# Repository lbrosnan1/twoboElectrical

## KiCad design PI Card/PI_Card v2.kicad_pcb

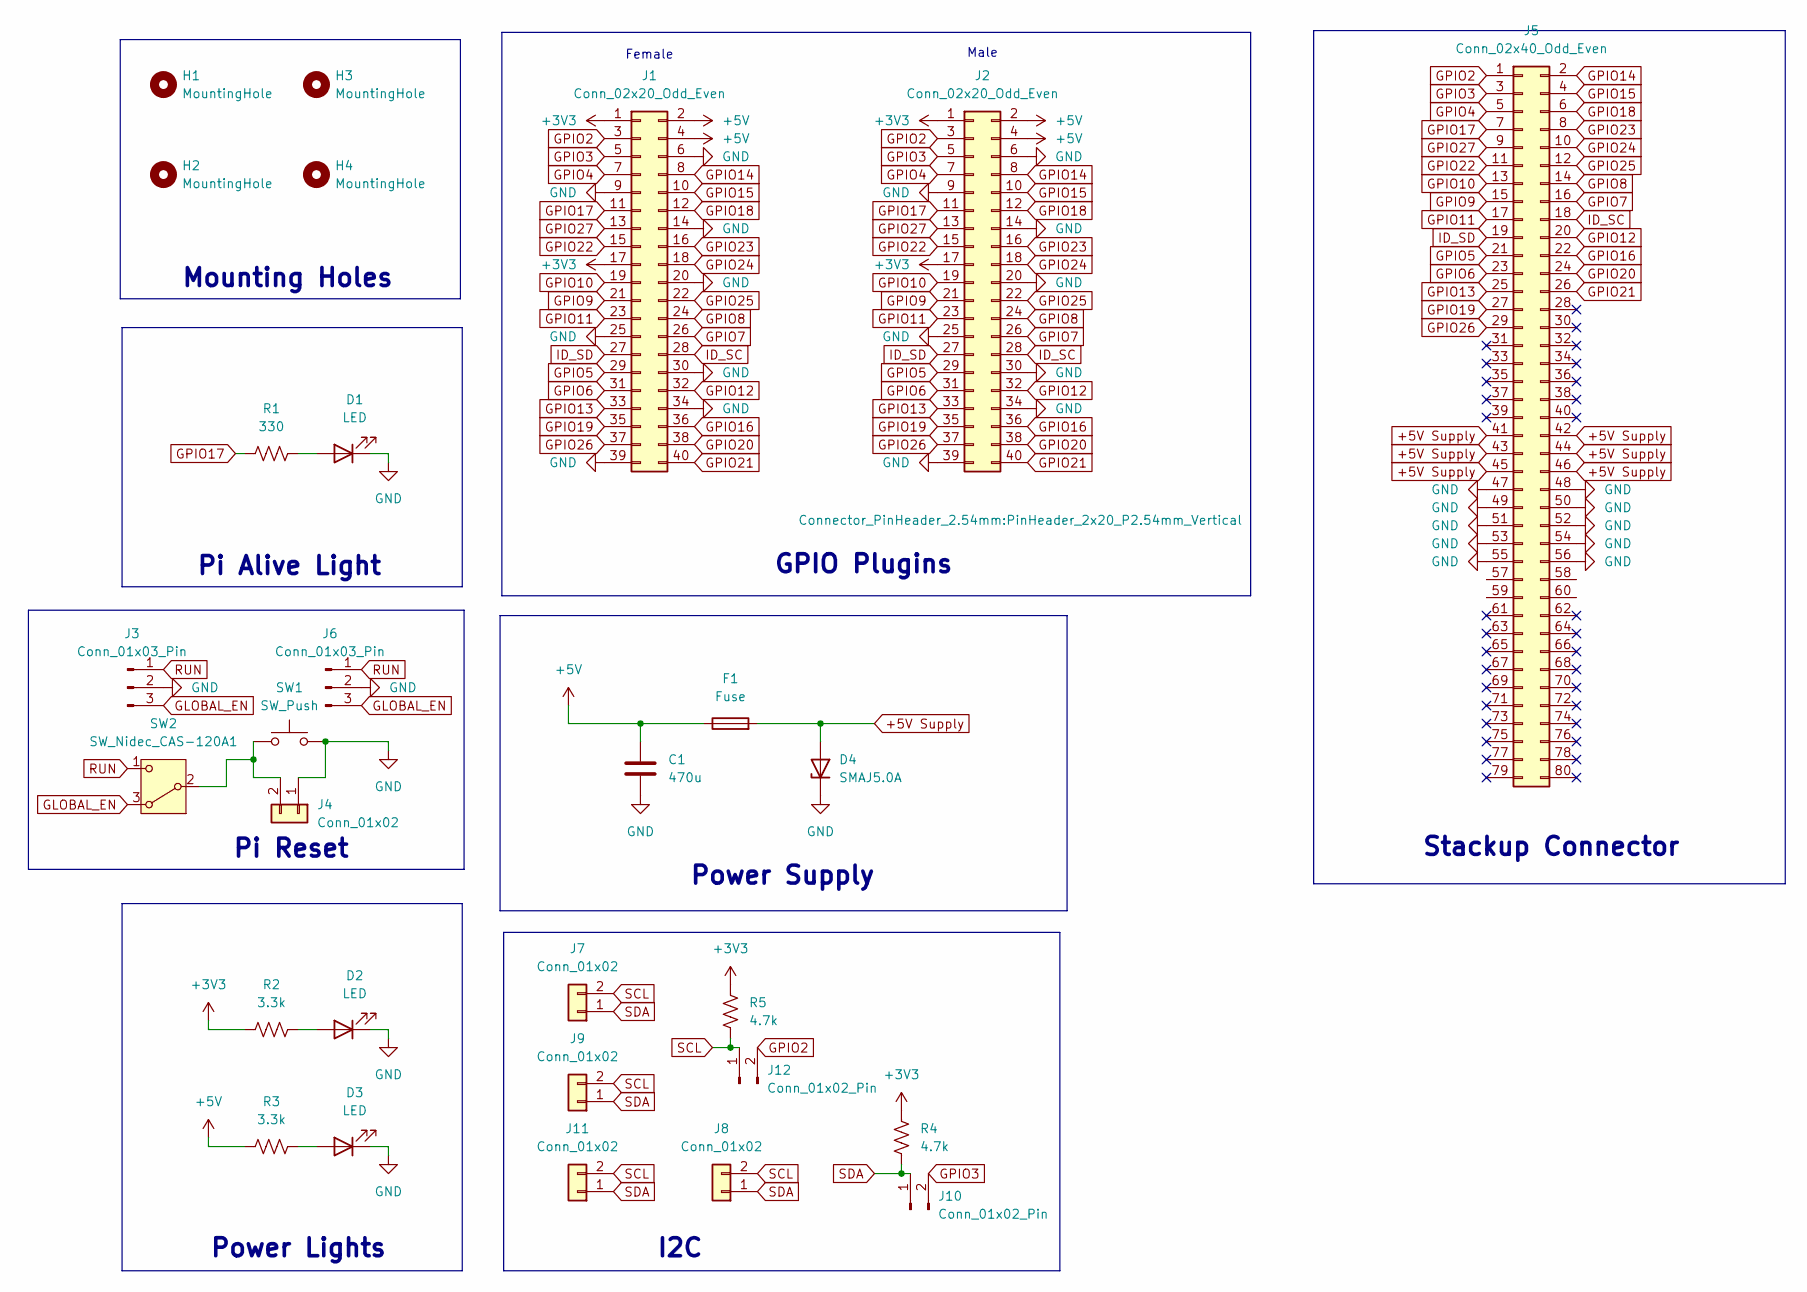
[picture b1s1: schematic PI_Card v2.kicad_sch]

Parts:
C1: 470u; CP_Radial_D10.0mm_P5.00mm
D1, D2, D3: LED; LED_D5.0mm
D4: SMAJ5.0A; D_SMA_Handsoldering
F1: Fuse; Fuseholder_Littelfuse_Nano2_154x_3D
H1, H2, H3, H4: MountingHole; MountingHole_2.2mm_M2
J1: Conn_02x20_Odd_Even; PinSocket_2x20_P2.54mm_Vertical
J2: Conn_02x20_Odd_Even; PinHeader_2x20_P2.54mm_Vertical
J3, J6: Conn_01x03_Pin; PinHeader_1x03_P2.54mm_Vertical
J4, J7, J8, J9, J11: Conn_01x02; JST_PH_B2B-PH-K_1x02_P2.00mm_Vertical
J5: Conn_02x40_Odd_Even; Samtec_HLE-140-02-L-DV-PE_2x40_P2.54mm_Horizontal
J10, J12: Conn_01x02_Pin; PinHeader_1x02_P2.54mm_Vertical
R1: 330; R_0805_2012Metric_Pad1.20x1.40mm_HandSolder
R2, R3: 3.3k; R_0805_2012Metric_Pad1.20x1.40mm_HandSolder
R4, R5: 4.7k; R_0805_2012Metric_Pad1.20x1.40mm_HandSolder
SW1: SW_Push; SW_PUSH_6mm
SW2: SW_Nidec_CAS-120A1; Nidec_Copal_CAS-120A

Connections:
+3V3: J1.1, J1.17, J2.1, J2.17, R2.1, R4.2, R5.2
+5V: C1.1, F1.1, J1.2, J1.4, J2.2, J2.4, R3.1
+5V Supply: D4.2 (A), F1.2, J5.41, J5.42, J5.43, J5.44, J5.45, J5.46
GLOBAL_EN: J3.3, J6.3, SW2.3 (A)
GND: C1.2, D1.1 (K), D2.1 (K), D3.1 (K), D4.1 (K), J1.6, J1.9, J1.14, J1.20, J1.25, J1.30, J1.34, J1.39, J2.6, J2.9, J2.14, J2.20, J2.25, J2.30, J2.34, J2.39, J3.2, J4.1, J5.47, J5.48, J5.49, J5.50, J5.51, J5.52, J5.53, J5.54, J5.55, J5.56, J6.2, SW1.2
GPIO2: J1.3, J2.3, J5.1, J12.2
GPIO3: J1.5, J2.5, J5.3, J10.2
GPIO4: J1.7, J2.7, J5.5
GPIO5: J1.29, J2.29, J5.21
GPIO6: J1.31, J2.31, J5.23
GPIO7: J1.26, J2.26, J5.16
GPIO8: J1.24, J2.24, J5.14
GPIO9: J1.21, J2.21, J5.15
GPIO10: J1.19, J2.19, J5.13
GPIO11: J1.23, J2.23, J5.17
GPIO12: J1.32, J2.32, J5.20
GPIO13: J1.33, J2.33, J5.25
GPIO14: J1.8, J2.8, J5.2
GPIO15: J1.10, J2.10, J5.4
GPIO16: J1.36, J2.36, J5.22
GPIO17: J1.11, J2.11, J5.7, R1.1
GPIO18: J1.12, J2.12, J5.6
GPIO19: J1.35, J2.35, J5.27
GPIO20: J1.38, J2.38, J5.24
GPIO21: J1.40, J2.40, J5.26
GPIO22: J1.15, J2.15, J5.11
GPIO23: J1.16, J2.16, J5.8
GPIO24: J1.18, J2.18, J5.10
GPIO25: J1.22, J2.22, J5.12
GPIO26: J1.37, J2.37, J5.29
GPIO27: J1.13, J2.13, J5.9
ID_SC: J1.28, J2.28, J5.18
ID_SD: J1.27, J2.27, J5.19
unnamed: D1.2 (A), R1.2
unnamed: D2.2 (A), R2.2
unnamed: D3.2 (A), R3.2
unnamed: J4.2, SW1.1, SW2.2 (B)
RUN: J3.1, J6.1, SW2.1 (C)
SCL: J7.2, J8.2, J9.2, J11.2, J12.1, R5.1
SDA: J7.1, J8.1, J9.1, J10.1, J11.1, R4.1

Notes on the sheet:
Female
Power Supply
Pi Reset
GPIO Plugins
Stackup Connector
Power Lights
Pi Alive Light
Male
I2C
Mounting Holes

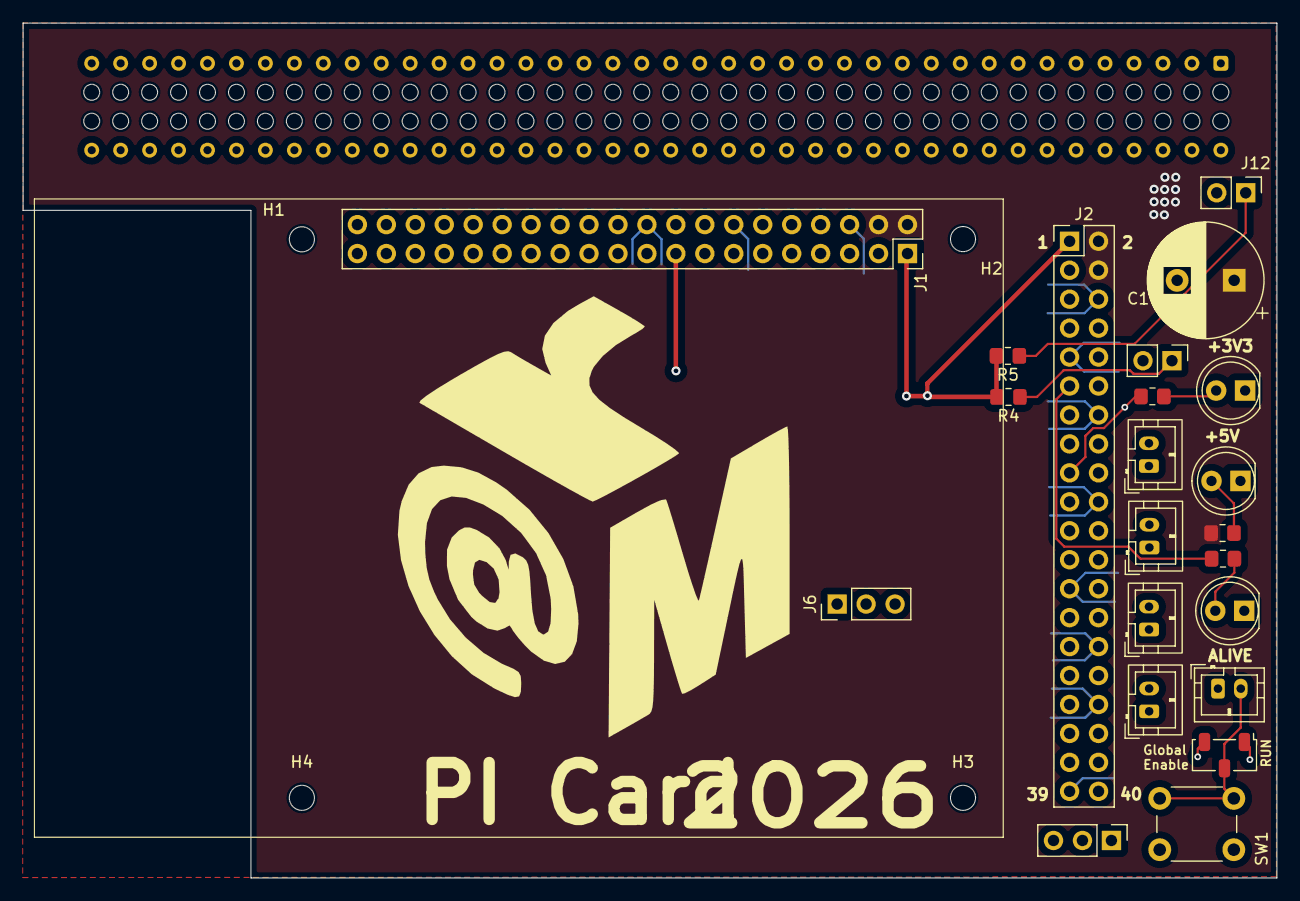
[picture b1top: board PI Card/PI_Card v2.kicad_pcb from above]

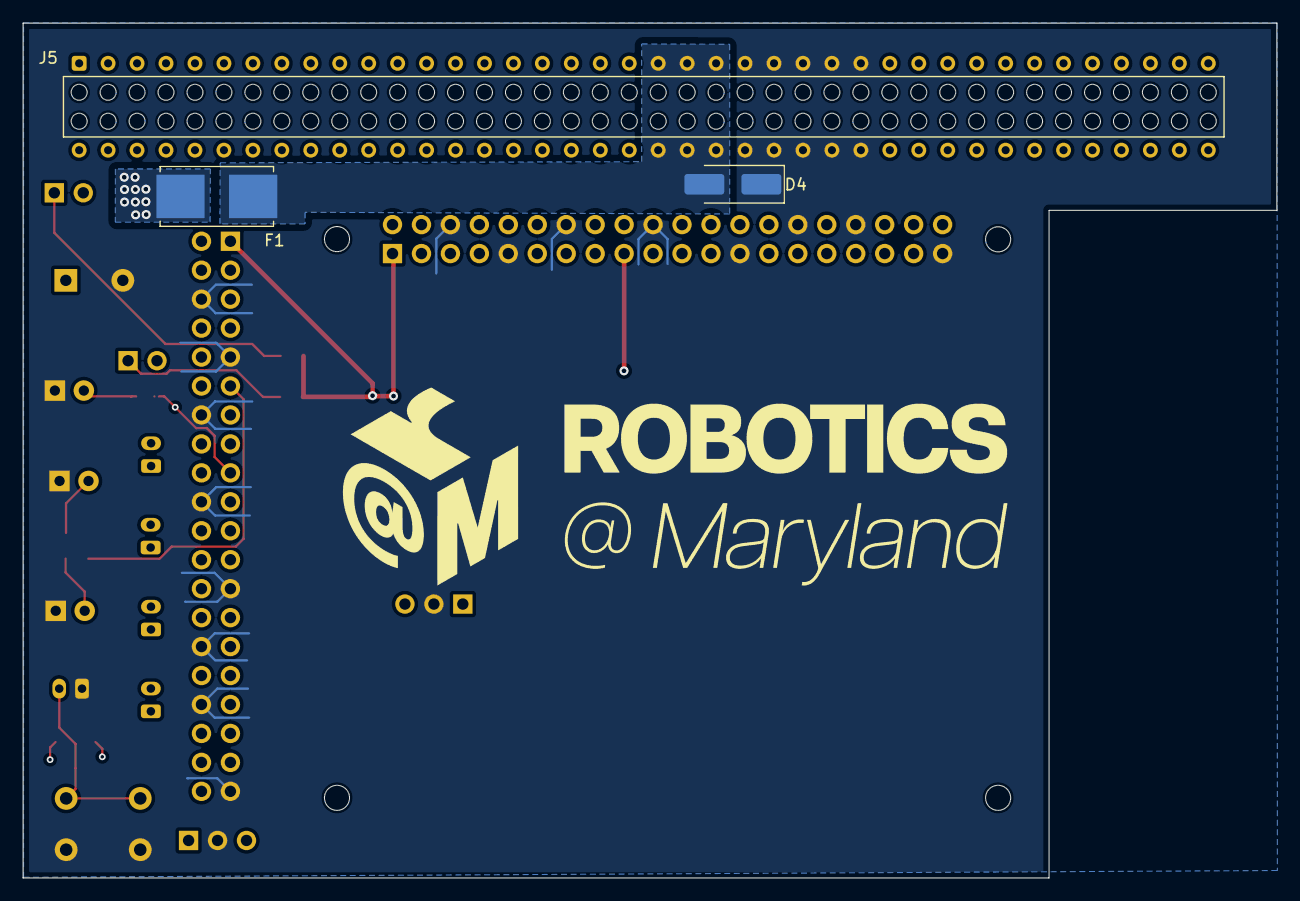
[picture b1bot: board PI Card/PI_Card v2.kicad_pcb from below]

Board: 4 copper layers, 110.0 x 75.0 mm, 29 parts (3 on the bottom side), 40 nets.

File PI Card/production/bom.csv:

Designator,Footprint,Quantity,Value,LCSC Part #
C1,CP_Radial_D10.0mm_P5.00mm,1,470u,
"D1, D2, D3",LED_D5.0mm,3,LED,
D4,D_SMA_Handsoldering,1,SMAJ5.0A,
F1,Fuseholder_Littelfuse_Nano2_154x_3D,1,Fuse,
J1,PinSocket_2x20_P2.54mm_Vertical,1,Conn_02x20_Odd_Even,
"J10, J12",PinHeader_1x02_P2.54mm_Vertical,2,Conn_01x02_Pin,
"J11, J4, J7, J8, J9",JST_PH_B2B-PH-K_1x02_P2.00mm_Vertical,5,Conn_01x02,
J2,PinHeader_2x20_P2.54mm_Vertical,1,Conn_02x20_Odd_Even,
"J3, J6",PinHeader_1x03_P2.54mm_Vertical,2,Conn_01x03_Pin,
J5,Samtec_HLE-140-02-L-DV-PE_2x40_P2.54mm_Horizontal,1,Conn_02x40_Odd_Even,
R1,0805,1,330,
"R2, R3",0805,2,3.3k,
"R4, R5",0805,2,4.7k,
SW1,SW_PUSH_6mm,1,SW_Push,
SW2,Nidec_Copal_CAS-120A,1,SW_Nidec_CAS-120A1,

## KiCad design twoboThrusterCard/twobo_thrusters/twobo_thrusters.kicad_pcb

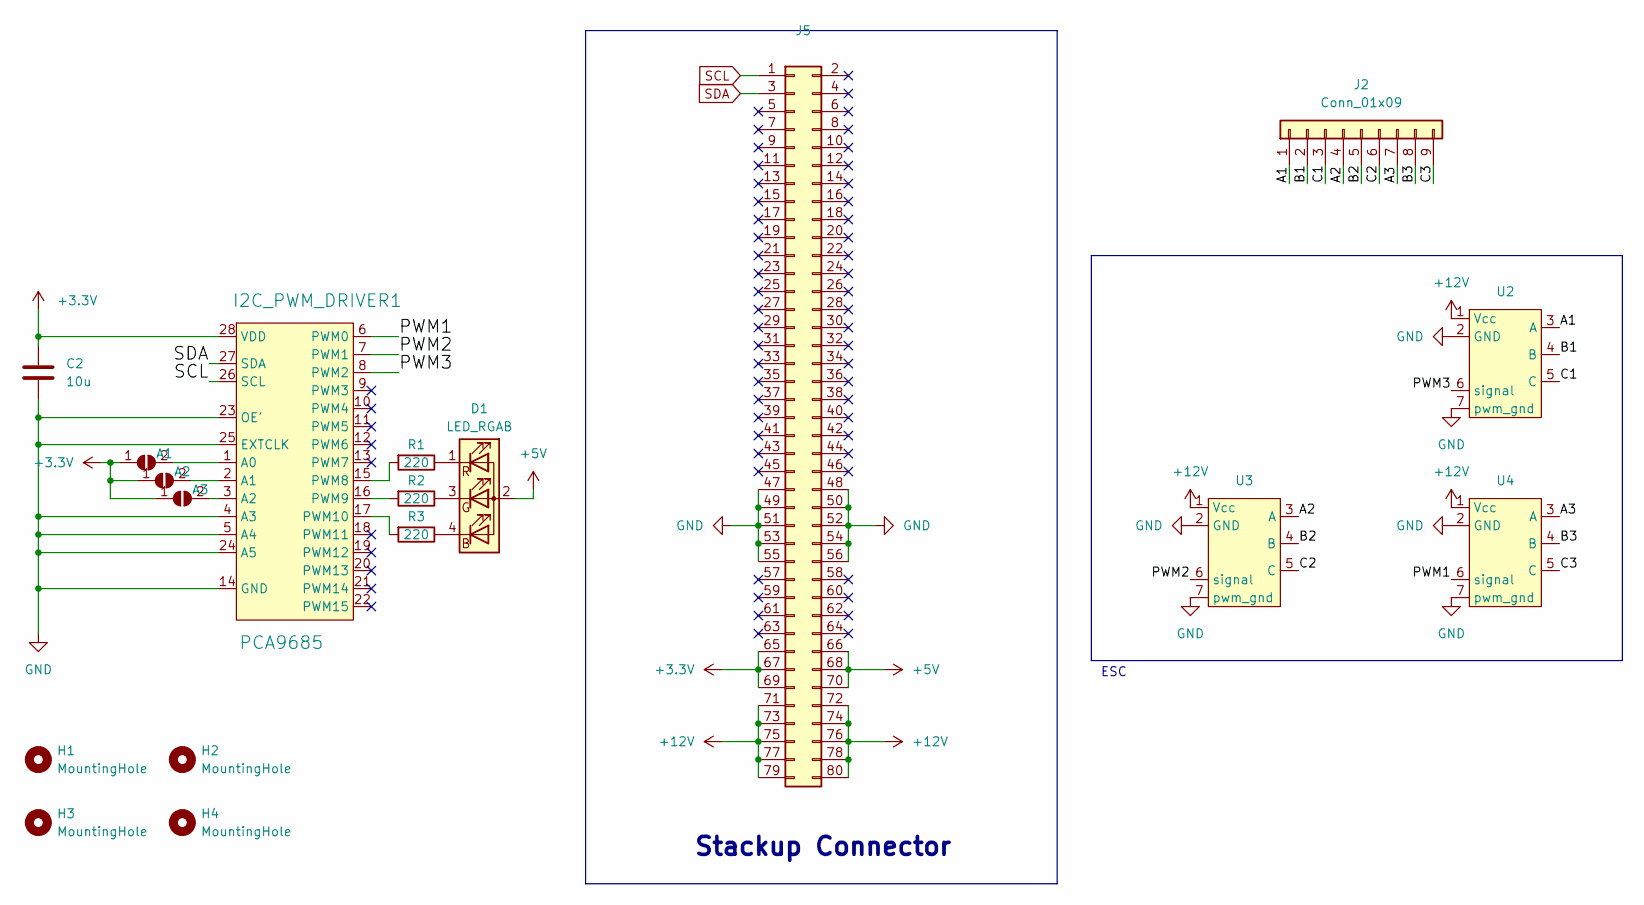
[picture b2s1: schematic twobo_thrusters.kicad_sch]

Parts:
A1, A2, A3: SolderJumper_2_Open; SolderJumper-2_P1.3mm_Open_TrianglePad1.0x1.5mm
C2: 10u; C_0805_2012Metric_Pad1.18x1.45mm_HandSolder
D1: LED_RGAB; LED_D5.0mm-4_RGB
H1, H2, H3, H4: MountingHole; MountingHole_2.2mm_M2
I2C_PWM_DRIVER1: PCA9685; TSSOP-28_4.4x9.7mm_P0.65mm
J2: Conn_01x09; Molex_Micro-Fit_3.0_43650-0900_1x09_P3.00mm_Horizontal
J5: Conn_02x40_Odd_Even; Samtec_HLE-140-02-L-DV-PE_2x40_P2.54mm_Horizontal
R1, R2, R3: 220; R_0805_2012Metric_Pad1.20x1.40mm_HandSolder
U2, U3, U4: ESC_blue_robotics

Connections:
+3.3V: A1.1 (A), A2.1 (A), A3.1 (A), C2.1, I2C_PWM_DRIVER1.28 (VDD), J5.65, J5.67, J5.69
+5V: D1.2 (A), J5.66, J5.68, J5.70
+12V: J5.71, J5.72, J5.73, J5.74, J5.75, J5.76, J5.77, J5.78, J5.79, J5.80, U2.1 (Vcc), U3.1 (Vcc), U4.1 (Vcc)
/A1: J2.1, U2.3 (A)
/A2: J2.4, U3.3 (A)
/A3: J2.7, U4.3 (A)
/B1: J2.2, U2.4 (B)
/B2: J2.5, U3.4 (B)
/B3: J2.8, U4.4 (B)
/C1: J2.3, U2.5 (C)
/C2: J2.6, U3.5 (C)
/C3: J2.9, U4.5 (C)
/PWM1: I2C_PWM_DRIVER1.6 (PWM0), U4.6 (signal)
/PWM2: I2C_PWM_DRIVER1.7 (PWM1), U3.6 (signal)
/PWM3: I2C_PWM_DRIVER1.8 (PWM2), U2.6 (signal)
GND: C2.2, I2C_PWM_DRIVER1.4 (A3), I2C_PWM_DRIVER1.5 (A4), I2C_PWM_DRIVER1.14 (GND), I2C_PWM_DRIVER1.23 (OE'), I2C_PWM_DRIVER1.24 (A5), I2C_PWM_DRIVER1.25 (EXTCLK), J5.47, J5.48, J5.49, J5.50, J5.51, J5.52, J5.53, J5.54, J5.55, J5.56, U2.2 (GND), U2.7 (pwm_gnd), U3.2 (GND), U3.7 (pwm_gnd), U4.2 (GND), U4.7 (pwm_gnd)
unnamed: A1.2 (B), I2C_PWM_DRIVER1.1 (A0)
unnamed: A2.2 (B), I2C_PWM_DRIVER1.2 (A1)
unnamed: A3.2 (B), I2C_PWM_DRIVER1.3 (A2)
unnamed: D1.4 (BK), R3.1
unnamed: D1.3 (GK), R2.1
unnamed: D1.1 (RK), R1.1
unnamed: I2C_PWM_DRIVER1.15 (PWM8), R1.2
unnamed: I2C_PWM_DRIVER1.16 (PWM9), R2.2
unnamed: I2C_PWM_DRIVER1.17 (PWM10), R3.2
SCL: I2C_PWM_DRIVER1.26 (SCL), J5.1
SDA: I2C_PWM_DRIVER1.27 (SDA), J5.3

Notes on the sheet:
ESC
Stackup Connector

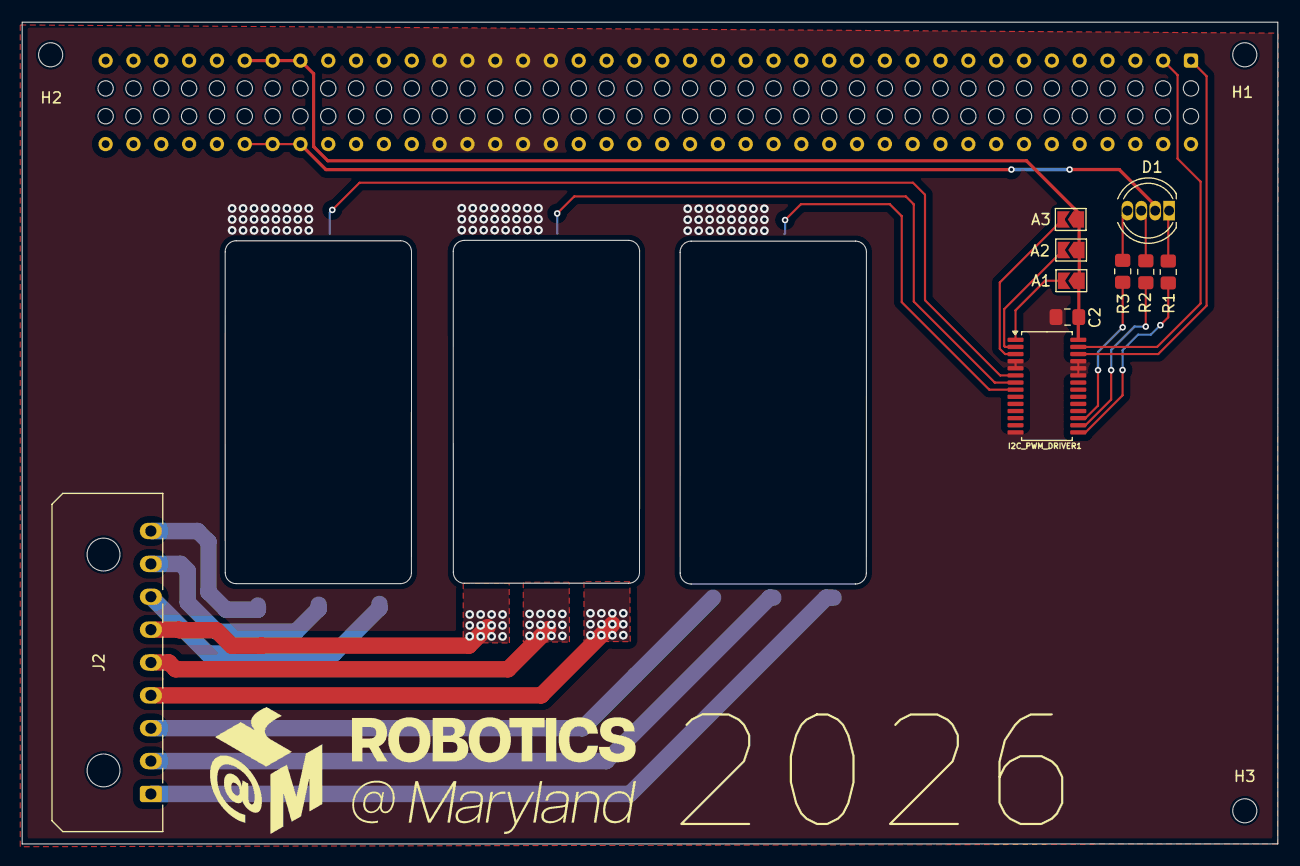
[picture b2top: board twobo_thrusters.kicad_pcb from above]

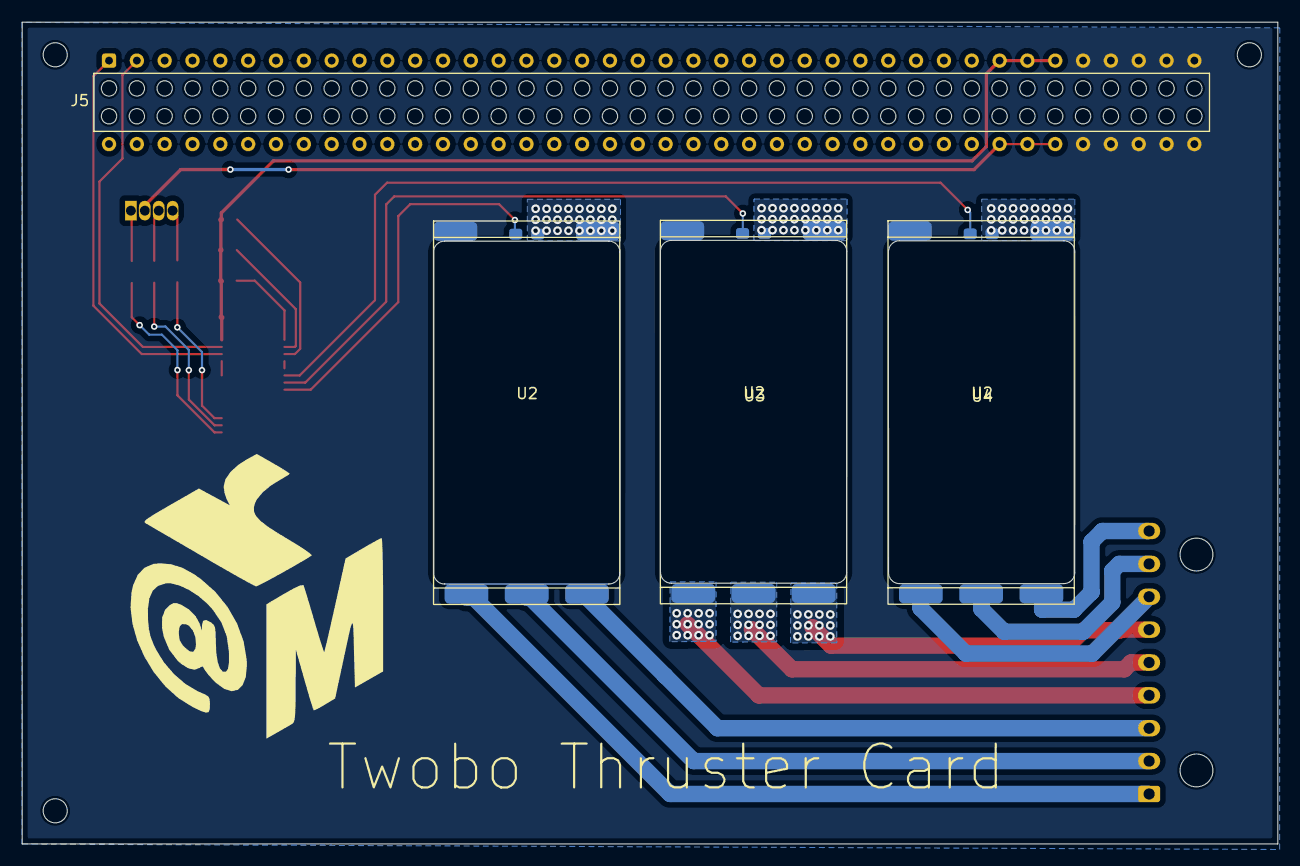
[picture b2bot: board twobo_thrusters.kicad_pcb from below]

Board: 2 copper layers, 114.5 x 75.0 mm, 17 parts (4 on the bottom side), 27 nets.

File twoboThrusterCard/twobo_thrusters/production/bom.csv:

Designator,Footprint,Quantity,Value,LCSC Part #
"A1, A2, A3",SolderJumper-2_P1.3mm_Open_TrianglePad1.0x1.5mm,3,SolderJumper_2_Open,
C2,0805,1,10u,
D1,LED_D5.0mm-4_RGB,1,LED_RGAB,
I2C_PWM_DRIVER1,TSSOP-28_4.4x9.7mm_P0.65mm,1,PCA9685,
J2,Molex_Micro-Fit_3.0_43650-0900_1x09_P3.00mm_Horizontal,1,Conn_01x09,
J5,Samtec_HLE-140-02-L-DV-PE_2x40_P2.54mm_Horizontal,1,Conn_02x40_Odd_Even,
"R1, R2, R3",0805,3,220,
"U2, U3, U4",ESC_blue_robotics,3,~,

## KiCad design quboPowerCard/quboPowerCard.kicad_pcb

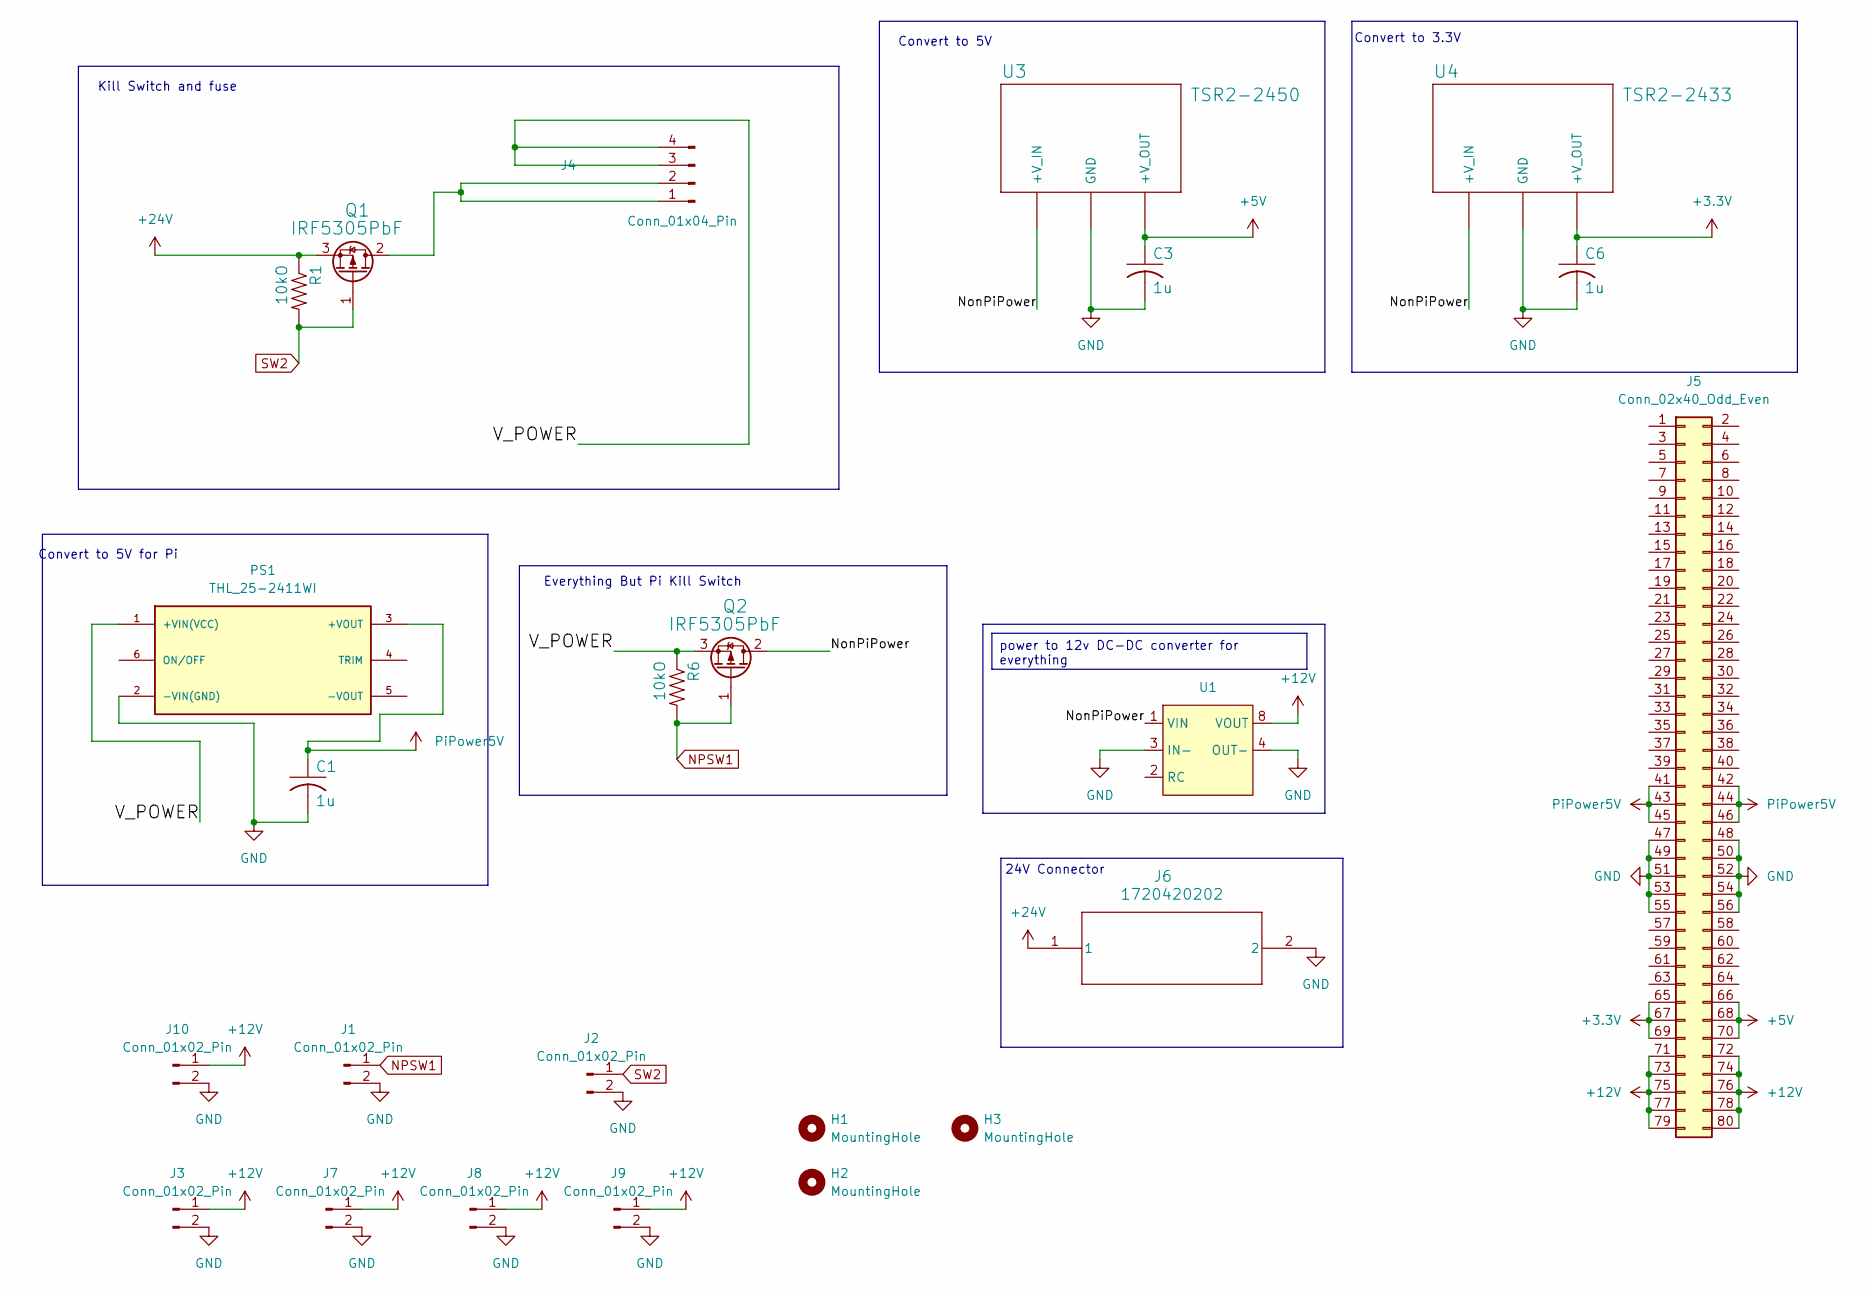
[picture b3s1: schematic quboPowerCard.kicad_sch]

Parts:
C1, C3, C6: 1u; C_0805_2012Metric_Pad1.18x1.45mm_HandSolder
H1, H2, H3: MountingHole; MountingHole_2.2mm_M2
J1, J2, J3, J7, J8, J9, J10: Conn_01x02_Pin; JST_PH_B2B-PH-K_1x02_P2.00mm_Vertical
J4: Conn_01x04_Pin; 1.25__FUSECLIPS
J5: Conn_02x40_Odd_Even; SAMTEC_HLE-140-02-L-DV-PE
J6: 1720420202; SUPERSABRE_2CIRCUIT
PS1: THL_25-2411WI; CONV_THL_25-2411WI; PARTREV Jan 18, 2021
Q1, Q2: IRF5305PbF; TO-220-3_Vertical
R1, R6: 10kO; R_0805_2012Metric_Pad1.20x1.40mm_HandSolder
U1: 240W_CONV
U3: TSR2-2450; CONV_TSR_2-2450
U4: TSR2-2433; CONV_TSR2-2433

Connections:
+3.3V: C6.1, J5.65, J5.67, J5.69, U4.3 (+V_OUT)
+5V: C3.1, J5.66, J5.68, J5.70, U3.3 (+V_OUT)
+12V: J3.1, J5.71, J5.72, J5.73, J5.74, J5.75, J5.76, J5.77, J5.78, J5.79, J5.80, J7.1, J8.1, J9.1, J10.1, U1.8 (VOUT)
+24V: J6.1, Q1.3 (S), R1.1
/NonPiPower: Q2.2 (D), U1.1 (VIN), U3.1 (+V_IN), U4.1 (+V_IN)
/V_POWER: J4.3, J4.4, PS1.1 (+VIN(VCC)), Q2.3 (S), R6.1
GND: C1.2, C3.2, C6.2, J1.2, J2.2, J3.2, J5.47, J5.48, J5.49, J5.50, J5.51, J5.52, J5.53, J5.54, J5.55, J5.56, J6.2, J7.2, J8.2, J9.2, J10.2, PS1.2 (-VIN(GND)), U1.3 (IN-), U1.4 (OUT-), U3.2 (GND), U4.2 (GND)
NPSW1: J1.1, Q2.1 (G), R6.2
unnamed: J4.1, J4.2, Q1.2 (D)
PiPower5V: C1.1, J5.41, J5.42, J5.43, J5.44, J5.45, J5.46, PS1.3 (+VOUT)
SW2: J2.1, Q1.1 (G), R1.2

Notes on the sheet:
Convert to 3.3V
Kill Switch and fuse
24V Connector
Convert to 5V
Convert to 5V for Pi
Everything But Pi Kill Switch
power to 12v DC-DC converter for everything

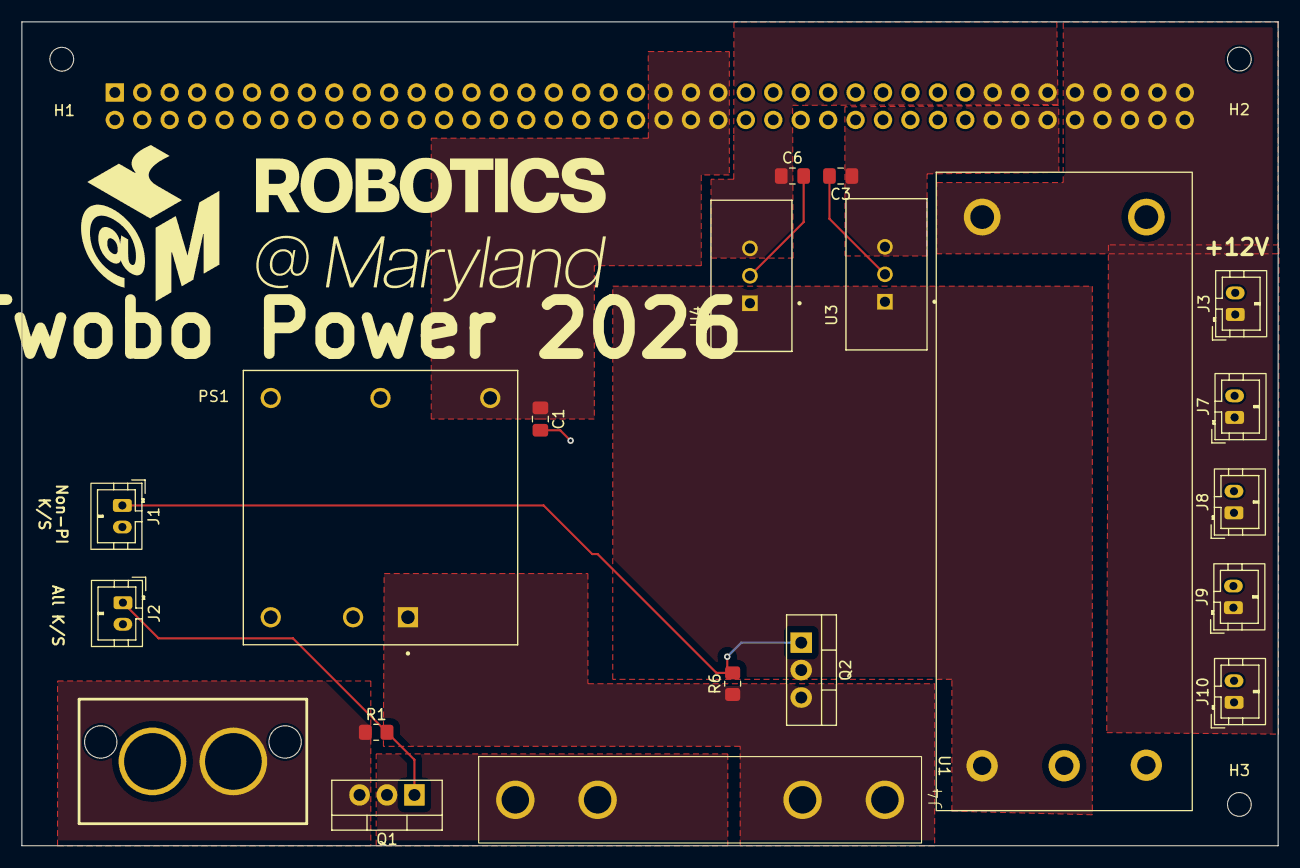
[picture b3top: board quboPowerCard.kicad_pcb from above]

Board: 2 copper layers, 116.3 x 76.3 mm, 24 parts (1 on the bottom side), 11 nets.

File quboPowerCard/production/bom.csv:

Designator,Footprint,Quantity,Value,LCSC Part #
"C1, C3, C6",0805,3,1u,
"J1, J10, J2, J3, J7, J8, J9",JST_PH_B2B-PH-K_1x02_P2.00mm_Vertical,7,Conn_01x02_Pin,
J4,1.25__FUSECLIPS,1,Conn_01x04_Pin,
J5,PinHeader_2x40_P2.54mm_Vertical,1,Conn_02x40_Odd_Even,
J6,SUPERSABRE_2CIRCUIT,1,1720420202,
PS1,CONV_THL_25-2411WI,1,THL_25-2411WI,
"Q1, Q2",TO-220-3_Vertical,2,IRF5305PbF,
"R1, R6",0805,2,10kO,
U1,240W_CONV,1,~,
U3,CONV_TSR_2-2450,1,TSR2-2450,
U4,CONV_TSR2-2433,1,TSR2-2433,

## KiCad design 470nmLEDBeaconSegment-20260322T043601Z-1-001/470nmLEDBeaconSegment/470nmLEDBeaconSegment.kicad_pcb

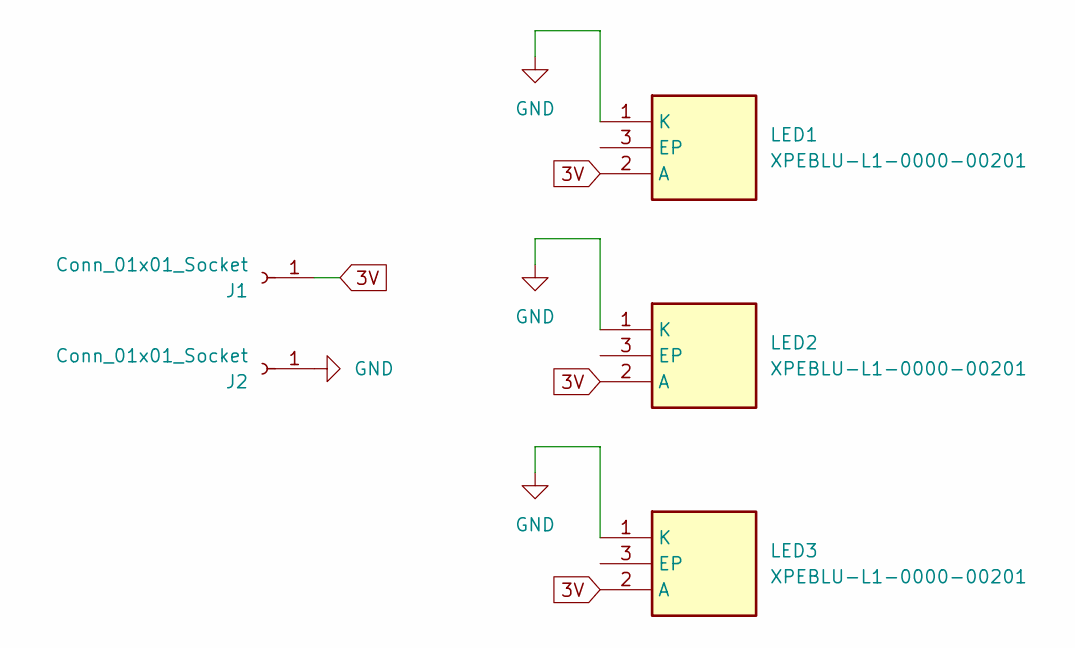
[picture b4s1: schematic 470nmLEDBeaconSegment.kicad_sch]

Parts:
J1, J2: Conn_01x01_Socket; Banana_Jack_1Pin
LED1, LED2, LED3: XPEBLU-L1-0000-00201; XPEBLUL1000000201; Manufacturer_Part_Number XPEBLU-L1-0000-00201; Mouser Part Number 941-XPEBLUL100201

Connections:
3V: J1.1, LED1.2 (A), LED2.2 (A), LED3.2 (A)
GND: J2.1, LED1.1 (K), LED2.1 (K), LED3.1 (K)

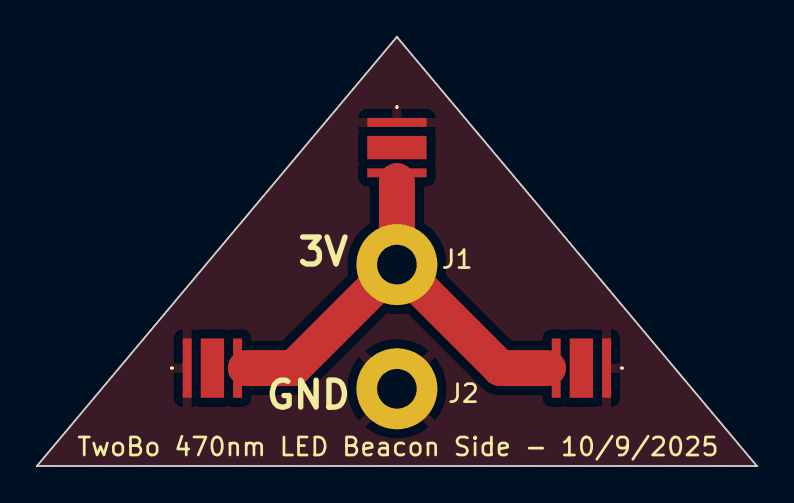
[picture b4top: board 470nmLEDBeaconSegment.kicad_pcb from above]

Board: 2 copper layers, 40.0 x 23.8 mm, 5 parts (0 on the bottom side), 2 nets.

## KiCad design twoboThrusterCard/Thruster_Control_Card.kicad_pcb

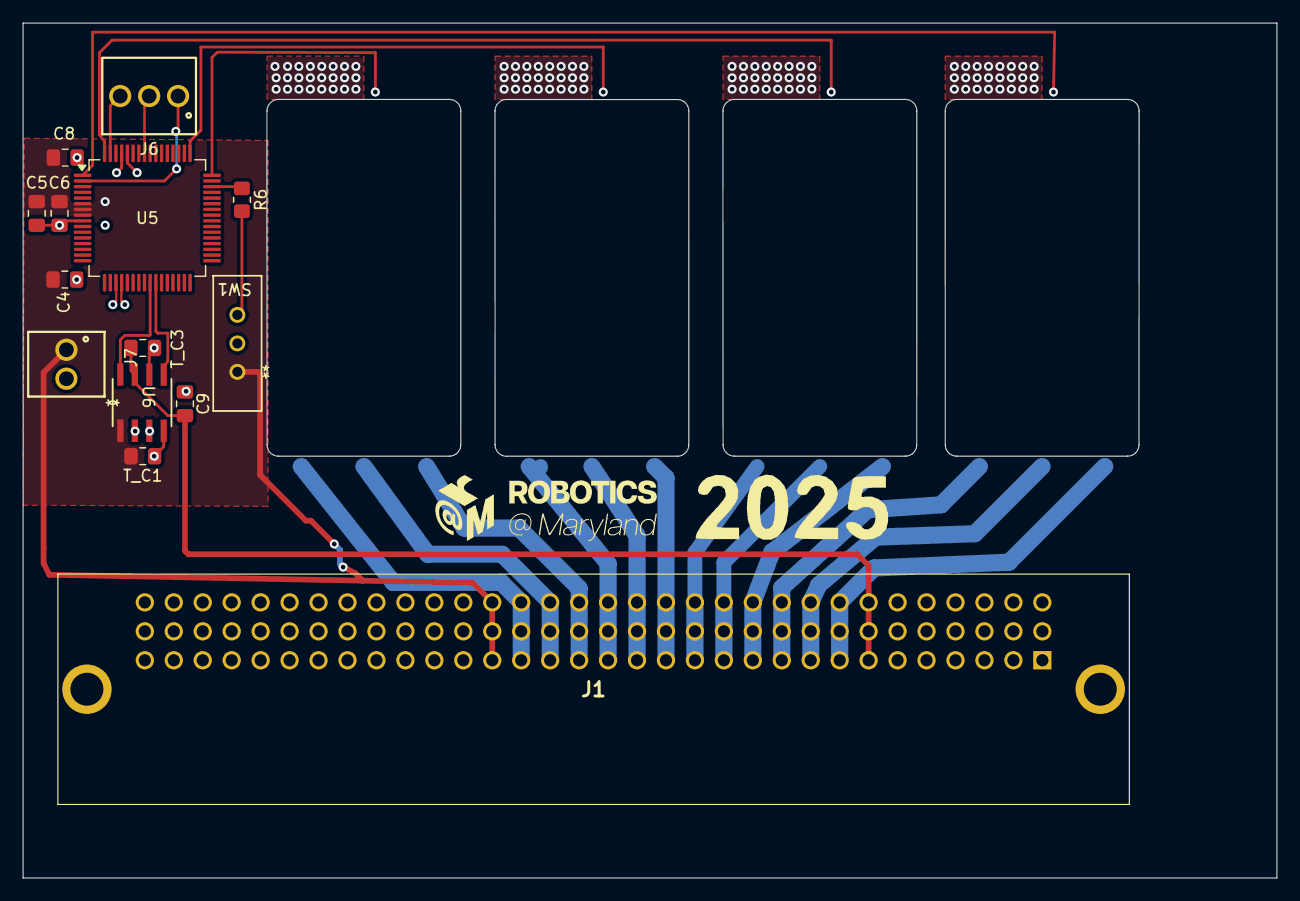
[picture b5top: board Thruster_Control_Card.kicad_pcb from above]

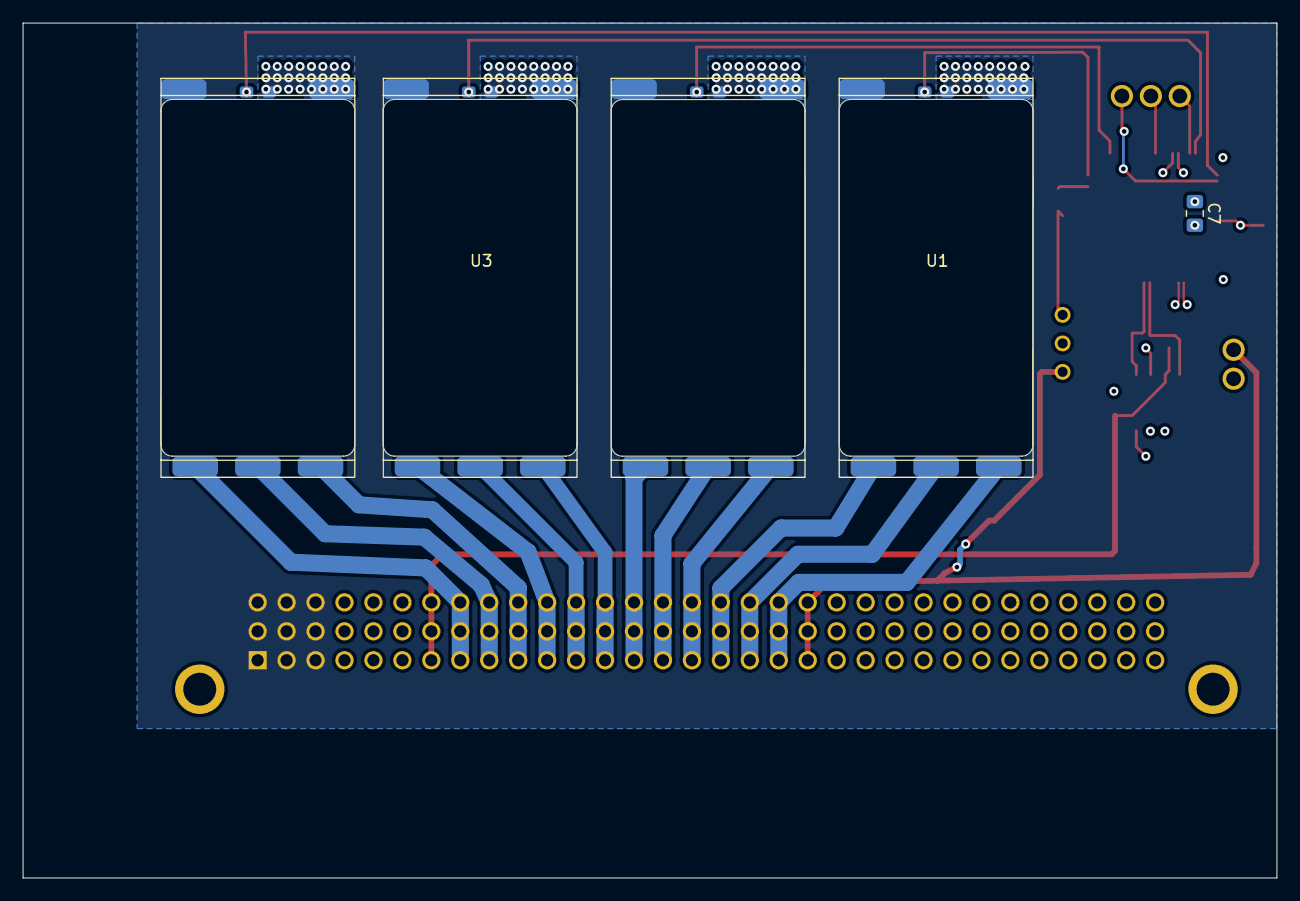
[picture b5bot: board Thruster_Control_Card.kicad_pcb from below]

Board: 4 copper layers, 109.9 x 75.0 mm, 19 parts (5 on the bottom side), 33 nets.

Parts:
C4: 4.7uF; C_0805_2012Metric_Pad1.18x1.45mm_HandSolder
C5, C6, C7: 100nF; C_0805_2012Metric_Pad1.18x1.45mm_HandSolder
C8: 1uF; C_0805_2012Metric_Pad1.18x1.45mm_HandSolder
C9: 22uF; C_0805_2012Metric_Pad1.18x1.45mm_HandSolder
J1: 6509475
J6: Screw_Terminal_01x03; screw_junc_254_3by1
J7: Screw_Terminal_01x02; screw_junc_254_2by1
R6: 10k; R_0805_2012Metric_Pad1.20x1.40mm_HandSolder
SW1: EG1218; slide_switch_EGER1218_Thruster
T_C1, T_C3: 100nF; C_0805_2012Metric_Pad1.18x1.45mm_HandSolder
U1, U2, U3, U4: ESC
U5: STM32G0B1RETx; LQFP-64_10x10mm_P0.5mm
U6: ATA6561-GAQW-N; SOIC8_4P9X3P9MC_MCH

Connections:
3.3v: C4.1, C5.2, C6.1, C7.1, C8.2, J1.A20, J1.B20, J1.C20, J7.1, SW1.1, T_C1.1, U5.6 (VBAT), U5.7 (VREF+), U5.8 (VDD), U6.5 (VIO)
5V: C9.1, J1.A7, J1.B7, J1.C7, T_C3.1, U6.3 (VCC)
+12V: J1.A1, J1.A2, J1.A3, J1.B1, J1.B2, J1.B3, J1.C1, J1.C2, J1.C3, U1.1 (Vcc), U2.1 (Vcc), U3.1 (Vcc), U4.1 (Vcc)
/A1: J1.A17, J1.B17, J1.C17, U1.3 (A)
/A2: J1.A14, J1.B14, J1.C14, U2.3 (A)
/A3: J1.A11, J1.B11, J1.C11, U3.3 (A)
/A4: J1.A8, J1.B8, J1.C8, U4.3 (A)
/B1: J1.A18, J1.B18, J1.C18, U1.4 (B)
/B2: J1.A15, J1.B15, J1.C15, U2.4 (B)
/B3: J1.A12, J1.B12, J1.C12, U3.4 (B)
/B4: J1.A9, J1.B9, J1.C9, U4.4 (B)
/C1: J1.A19, J1.B19, J1.C19, U1.5 (C)
/C2: J1.A16, J1.B16, J1.C16, U2.5 (C)
/C3: J1.A13, J1.B13, J1.C13, U3.5 (C)
/C4: J1.A10, J1.B10, J1.C10, U4.5 (C)
/NRST: J6.2, U5.57 (PB3)
/SCL_IN: J1.B32, J1.C32, U5.60 (PB6)
/SDA_IN: J1.A31, J1.B31, U5.61 (PB7)
/SWCLK: J6.3, U5.63 (PB9)
/SWDIO: J6.1, U5.2 (PC12)
CAN+: J1.B27, U6.7 (CANH)
CAN-: J1.C28, U6.6 (CANL)
FDCAN_RX: U5.25 (PC4), U6.4 (RXD)
FDCAN_TX: U5.26 (PC5), U6.1 (TXD)
GND: C4.2, C5.1, C6.2, C7.2, C8.1, C9.2, J1.A4, J1.A5, J1.A6, J1.A26, J1.A28, J1.A30, J1.A32, J1.B4, J1.B5, J1.B6, J1.C4, J1.C5, J1.C6, J1.C25, J1.C27, J1.C29, J1.C31, J7.2, SW1.2, T_C1.2, T_C3.2, U1.2 (GND), U1.7 (pwm_gnd), U2.2 (GND), U2.7 (pwm_gnd), U3.2 (GND), U3.7 (pwm_gnd), U4.2 (GND), U4.7 (pwm_gnd), U5.9 (VSS), U6.2 (GND), U6.8 (STBY)
unnamed: R6.2, SW1.3
unnamed: R6.1, U5.46 (PA14)
TIM1 CH2 (PWM): U2.6 (signal), U5.49 (PC9)
TIM1 CH3 (PWM): U3.6 (signal), U5.64 (PC10)
TIM1 CH4 (PWM): U4.6 (signal), U5.1 (PC11)
TIM1 CH (PWM): U1.6 (signal), U5.48 (PC8)
USART2+: J1.C26, U5.19 (PA2)
USART2-: J1.B25, U5.20 (PA3)
